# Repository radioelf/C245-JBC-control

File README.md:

# C245 JBC control

 Harware y sofware para el control de soldadores JBC con puntas del tipo C245
 el  harware se ha realizado con KiCad y el sofware para un Arduino Mega.

 Obsoleto,recomendado: https://github.com/AxxAxx/AxxSolder

Creative Commons License Disclaimer

UNLESS OTHERWISE MUTUALLY AGREED TO BY THE PARTIES IN WRITING, LICENSOR OFFERS THE WORK AS-IS AND MAKES NO REPRESENTATIONS OR WARRANTIES OF ANY KIND CONCERNING THE WORK, EXPRESS, IMPLIED, STATUTORY OR OTHERWISE, INCLUDING, WITHOUT LIMITATION, WARRANTIES OF TITLE, MERCHANTIBILITY, FITNESS FOR A PARTICULAR PURPOSE, NONINFRINGEMENT, OR THE ABSENCE OF LATENT OR OTHER DEFECTS, ACCURACY, OR THE PRESENCE OF ABSENCE OF ERRORS, WHETHER OR NOT DISCOVERABLE. SOME JURISDICTIONS DO NOT ALLOW THE EXCLUSION OF IMPLIED WARRANTIES, SO SUCH EXCLUSION MAY NOT APPLY TO YOU. EXCEPT TO THE EXTENT REQUIRED BY APPLICABLE LAW, IN NO EVENT WILL LICENSOR BE LIABLE TO YOU ON ANY LEGAL THEORY FOR ANY SPECIAL, INCIDENTAL, CONSEQUENTIAL, PUNITIVE OR EXEMPLARY DAMAGES ARISING OUT OF THIS LICENSE OR THE USE OF THE WORK, EVEN IF LICENSOR HAS BEEN ADVISED OF THE POSSIBILITY OF SUCH DAMAGES.

http://creativecommons.org/licenses/by-sa/3.0/

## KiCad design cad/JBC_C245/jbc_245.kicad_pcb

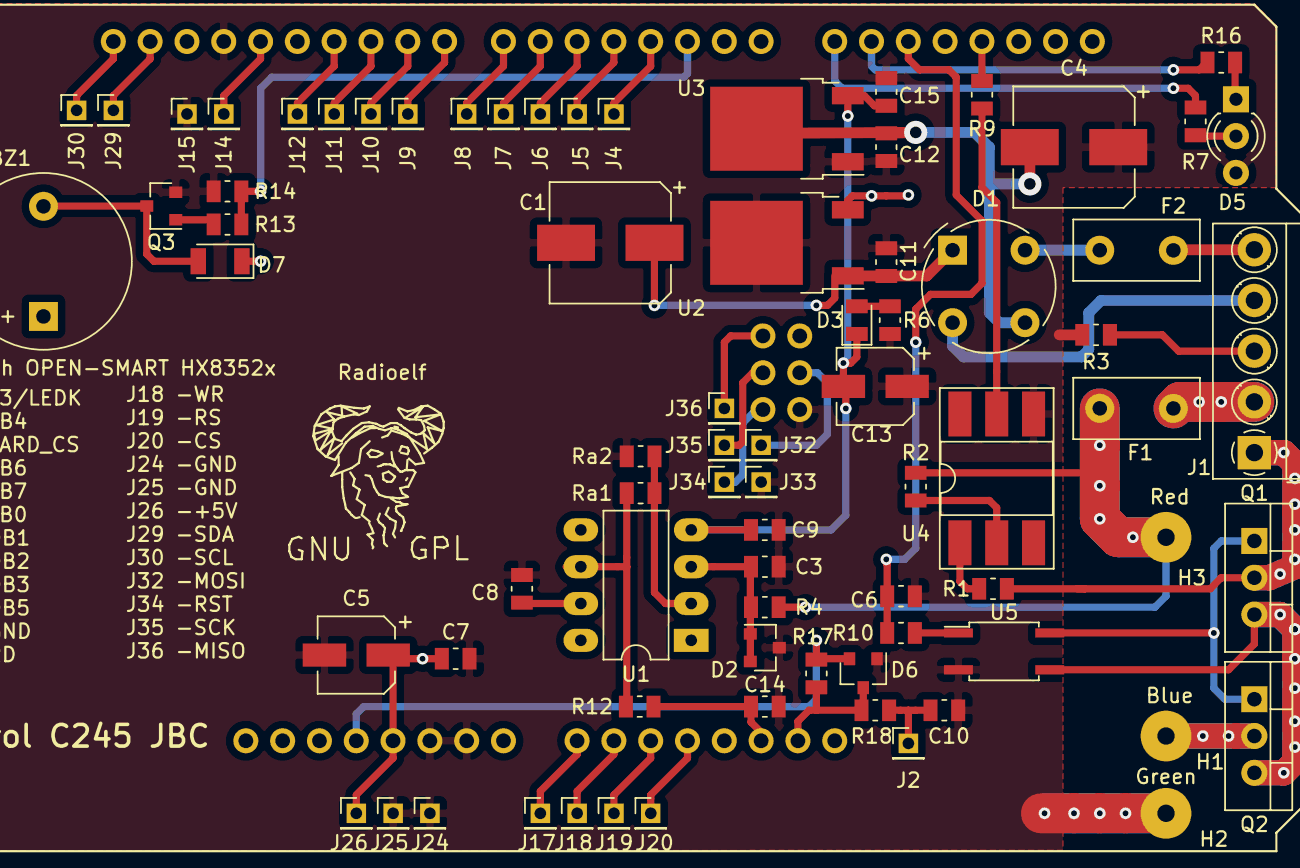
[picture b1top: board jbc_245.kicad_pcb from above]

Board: 2 copper layers, 79 parts (0 on the bottom side), 54 nets.

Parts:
BZ1: Buzzer; Buzzer_12x9.5RM7.6
C1, C4: 220uF 25V; CP_Elec_8x10
C3, C6: 1nF; C_0805_2012Metric
C5, C13: 100uF; CP_Elec_5x4.5
C7, C8, C9, C10, C11, C12, C15: 100nF; C_0805_2012Metric
C14: 10nF; C_0805_2012Metric
D1: Bridge; Diode_Bridge_Round_D9.0mm
D2, D6: BAV199; D_SOT-23_BAV199
D3: LED; LED_0805_2012Metric
D5: LED_Dual; LED_D3.0mm-3
D7: 1N4148; D_1206_3216Metric
F1: 6A; Fuse_Littlefuse_395Series
F2: 0.5A; Fuse_Littlefuse_395Series
H1: Blue-C245; SolderWirePad_single_1-2mmDrill
H2: Green-C245; SolderWirePad_single_1-2mmDrill
H3: RED-C245; SolderWirePad_single_1-2mmDrill
J1: Power AC; TerminalBlock_MetzConnect_Type059_RT06305HBWC_1x05_P3.50mm_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
J2: Sleep; PinHeader_1x01_P2.00mm_Vertical
J4: LCD-D3; PinHeader_1x01_P2.00mm_Vertical
J5: LCD-DB4; PinHeader_1x01_P2.00mm_Vertical
J6: SD_CS; PinHeader_1x01_P2.00mm_Vertical
J7: LCD-D6_X+; PinHeader_1x01_P2.00mm_Vertical
J8: LCD-D7_Y-; PinHeader_1x01_P2.00mm_Vertical
J9: LCD-D0; PinHeader_1x01_P2.00mm_Vertical
J10: LCD-D; PinHeader_1x01_P2.00mm_Vertical
J11: DB2; PinHeader_1x01_P2.00mm_Vertical
J12: DB3; PinHeader_1x01_P2.00mm_Vertical
J14: DB5; PinHeader_1x01_P2.00mm_Vertical
J15, J24, J25, J33: GND-LCD; PinHeader_1x01_P2.00mm_Vertical
J17: LCD-RD; PinHeader_1x01_P2.00mm_Vertical
J18: LCD-WR_Y+; PinHeader_1x01_P2.00mm_Vertical
J19: LCD-RS_X-; PinHeader_1x01_P2.00mm_Vertical
J20: LCD-CS; PinHeader_1x01_P2.00mm_Vertical
J26: +5V-LCD; PinHeader_1x01_P2.00mm_Vertical
J29: SDA-LM75; PinHeader_1x01_P2.00mm_Vertical
J30: SCL-LM75; PinHeader_1x01_P2.00mm_Vertical
J32: SD-MOSI-LCD; PinHeader_1x01_P2.00mm_Vertical
J34: LCD-RST; PinHeader_1x01_P2.00mm_Vertical
J35: SD-SCK-LCD; PinHeader_1x01_P2.00mm_Vertical
J36: SD-MISO-LCD; PinHeader_1x01_P2.00mm_Vertical
Q1, Q2: BUZ11; TO-220-3_Vertical
Q3: BSS138; SOT-23
R1, R2: 2K2; R_0805_2012Metric
R3: 0R; R_0805_2012Metric
R4, R12, R14: 10K; R_0805_2012Metric
R6: 1K; R_0805_2012Metric
R7, R13, R16: 470R; R_0805_2012Metric
R9: 330R; R_0805_2012Metric
R10: 330; R_0805_2012Metric
R17: 6M5; R_0805_2012Metric
R18: 1k8; R_0805_2012Metric
Ra1: 100K; R_0805_2012Metric
Ra2: 330R; R_0805_2012Metric
Radioelf: Symbol_GNU-Logo_SilkscreenTop
U1: OPA177; DIP-8_W7.62mm_LongPads
U2: LM7805_TO252; TO-252-2
U3: MC79M05_TO252; TO-252-2
U4: H11AA1-X009T; DIP-6_W8.89mm_SMDSocket_LongPads
U5: VOM1271T; SO-4_4.4x3.6mm_P2.54mm
XA1: Arduino_Mega2560_Shield; Arduino_Mega2560_MOD

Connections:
0V: C1.2, C3.2, C4.1, C5.2, C6.1, C7.2, C8.1, C9.1, C10.2, C11.2, C12.1, C13.1, C14.2, C15.1, D2.2, D5.3, D6.1, H2.1, J15.1, J24.1, J25.1, J33.1, Q3.2, R3.2, R6.2, R14.1, Ra2.1, U2.2, U3.1, U4.4, U5.2, XA1.GND1, XA1.GND2, XA1.GND3, XA1.GND4
+3V3: D6.3, R17.1, XA1.3V3
+5V: BZ1.1, C5.1, C7.1, C8.2, D7.1, J26.1, U1.7, U2.3, XA1.5V1, XA1.5V2
-5V: C9.2, C13.2, C15.2, D3.1, U1.4, U3.3
Control: C6.2, R10.1, XA1.D16
unnamed: BZ1.2, D7.2, Q3.3
unnamed: C1.1, C11.1, D1.1, U2.1
unnamed: C3.1, D2.1, D2.3, R4.1, U1.3
unnamed: C10.1, J2.1, R18.2
unnamed: C4.2, C12.2, D1.3, U3.2
unnamed: D1.2, J1.4
unnamed: D1.4, F2.1
unnamed: D3.2, R6.1
unnamed: D5.1, R16.2
unnamed: D5.2, R7.2
unnamed: D6.2, R17.2, R18.1, XA1.A6
unnamed: F1.1, J1.2
unnamed: F1.2, H3.1, R2.2, R4.2
unnamed: F2.2, J1.5
unnamed: H1.1, Q2.2
unnamed: J1.1, Q1.2, R1.2
unnamed: J1.3, R3.1
unnamed: J4.1, XA1.D3
unnamed: J5.1, XA1.D4
unnamed: J6.1, XA1.D5
unnamed: J7.1, XA1.D6
unnamed: J8.1, XA1.D7
unnamed: J9.1, XA1.D8
unnamed: J10.1, XA1.D9
unnamed: J11.1, XA1.D10
unnamed: J12.1, XA1.D11
unnamed: J14.1, XA1.D13
unnamed: J17.1, XA1.A0
unnamed: J18.1, XA1.A1
unnamed: J19.1, XA1.A2
unnamed: J20.1, XA1.A3
unnamed: J32.1, XA1.MOSI
unnamed: J34.1, XA1.RST2
unnamed: J35.1, XA1.SCK
unnamed: J36.1, XA1.MISO
unnamed: Q1.1, Q2.1, U5.4
unnamed: Q1.3, Q2.3, U5.3
unnamed: Q3.1, R13.2
unnamed: R1.1, U4.1
unnamed: R2.1, U4.2
unnamed: R7.1, XA1.D14
unnamed: R9.1, U4.5
unnamed: R10.2, U5.1
unnamed: R12.2, Ra1.1, U1.6
unnamed: R13.1, R14.2, XA1.D2
unnamed: R16.1, XA1.D15
unnamed: Ra1.2, Ra2.2, U1.2
Paso_Cero: R9.2, XA1.D18
Temperatura_JBC: C14.1, R12.1, XA1.A5

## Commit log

2019-02-19 Control soldador JBC c245
2019-02-20 Esquema-pdf
2019-02-22 Update tft.h
    Off botón + mensaje STOP
2026-02-12 Obsoleto
    look: https://github.com/AxxAxx/AxxSolder
